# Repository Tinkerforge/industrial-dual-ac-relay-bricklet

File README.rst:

Industrial Dual AC Relay Bricklet
=================================

This repository contains the firmware source code and the hardware design
files. The documentation generator configs can be found at
https://github.com/Tinkerforge/generators

Repository Content
------------------

software/:
 * examples/: Examples for all supported languages
 * build/: Compiled files
 * src/: Source code of firmware
 * Makefile: Makefile to build project

hardware/:
 * Contains KiCad project files and additionally schematics as PDF

datasheets/:
 * Contains datasheets for sensors and complex ICs that are used

Hardware
--------

The hardware is designed with the open source EDA Suite KiCad
(http://www.kicad.org). Before you are able to open the files,
you have to install the Tinkerforge kicad-libraries
(https://github.com/Tinkerforge/kicad-libraries). You can either clone
them directly in hardware/ or clone them in a separate folder and
symlink them into hardware/
(ln -s kicad_path/kicad-libraries project_path/hardware). After that you
can open the .pro file in hardware/ with KiCad and from there view and
modify the schematics and the PCB layout.

Software
--------

If you want to do your own Brick/Bricklet firmware development we highly
recommend that you use our build environment setup script and read the
tutorial (https://www.tinkerforge.com/en/doc/Tutorials/Tutorial_Build_Environment/Tutorial.html).

To compile the C code we recommend you to install the newest GNU Arm Embedded
Toolchain (https://launchpad.net/gcc-arm-embedded/+download).
You also need to install bricklib2 (https://github.com/Tinkerforge/bricklib2).

You can either clone it directly in software/src/ or clone it in a
separate folder and symlink it into software/src/
(ln -s bricklib_path/bricklib2 project_path/software/src/). Finally make sure to
have CMake installed (http://www.cmake.org/cmake/resources/software.html).

After that you can build the firmware by invoking make in software/.
The firmware (.zbin) can then be found in software/build/ and uploaded
with brickv (click button "Flashing" on start screen).

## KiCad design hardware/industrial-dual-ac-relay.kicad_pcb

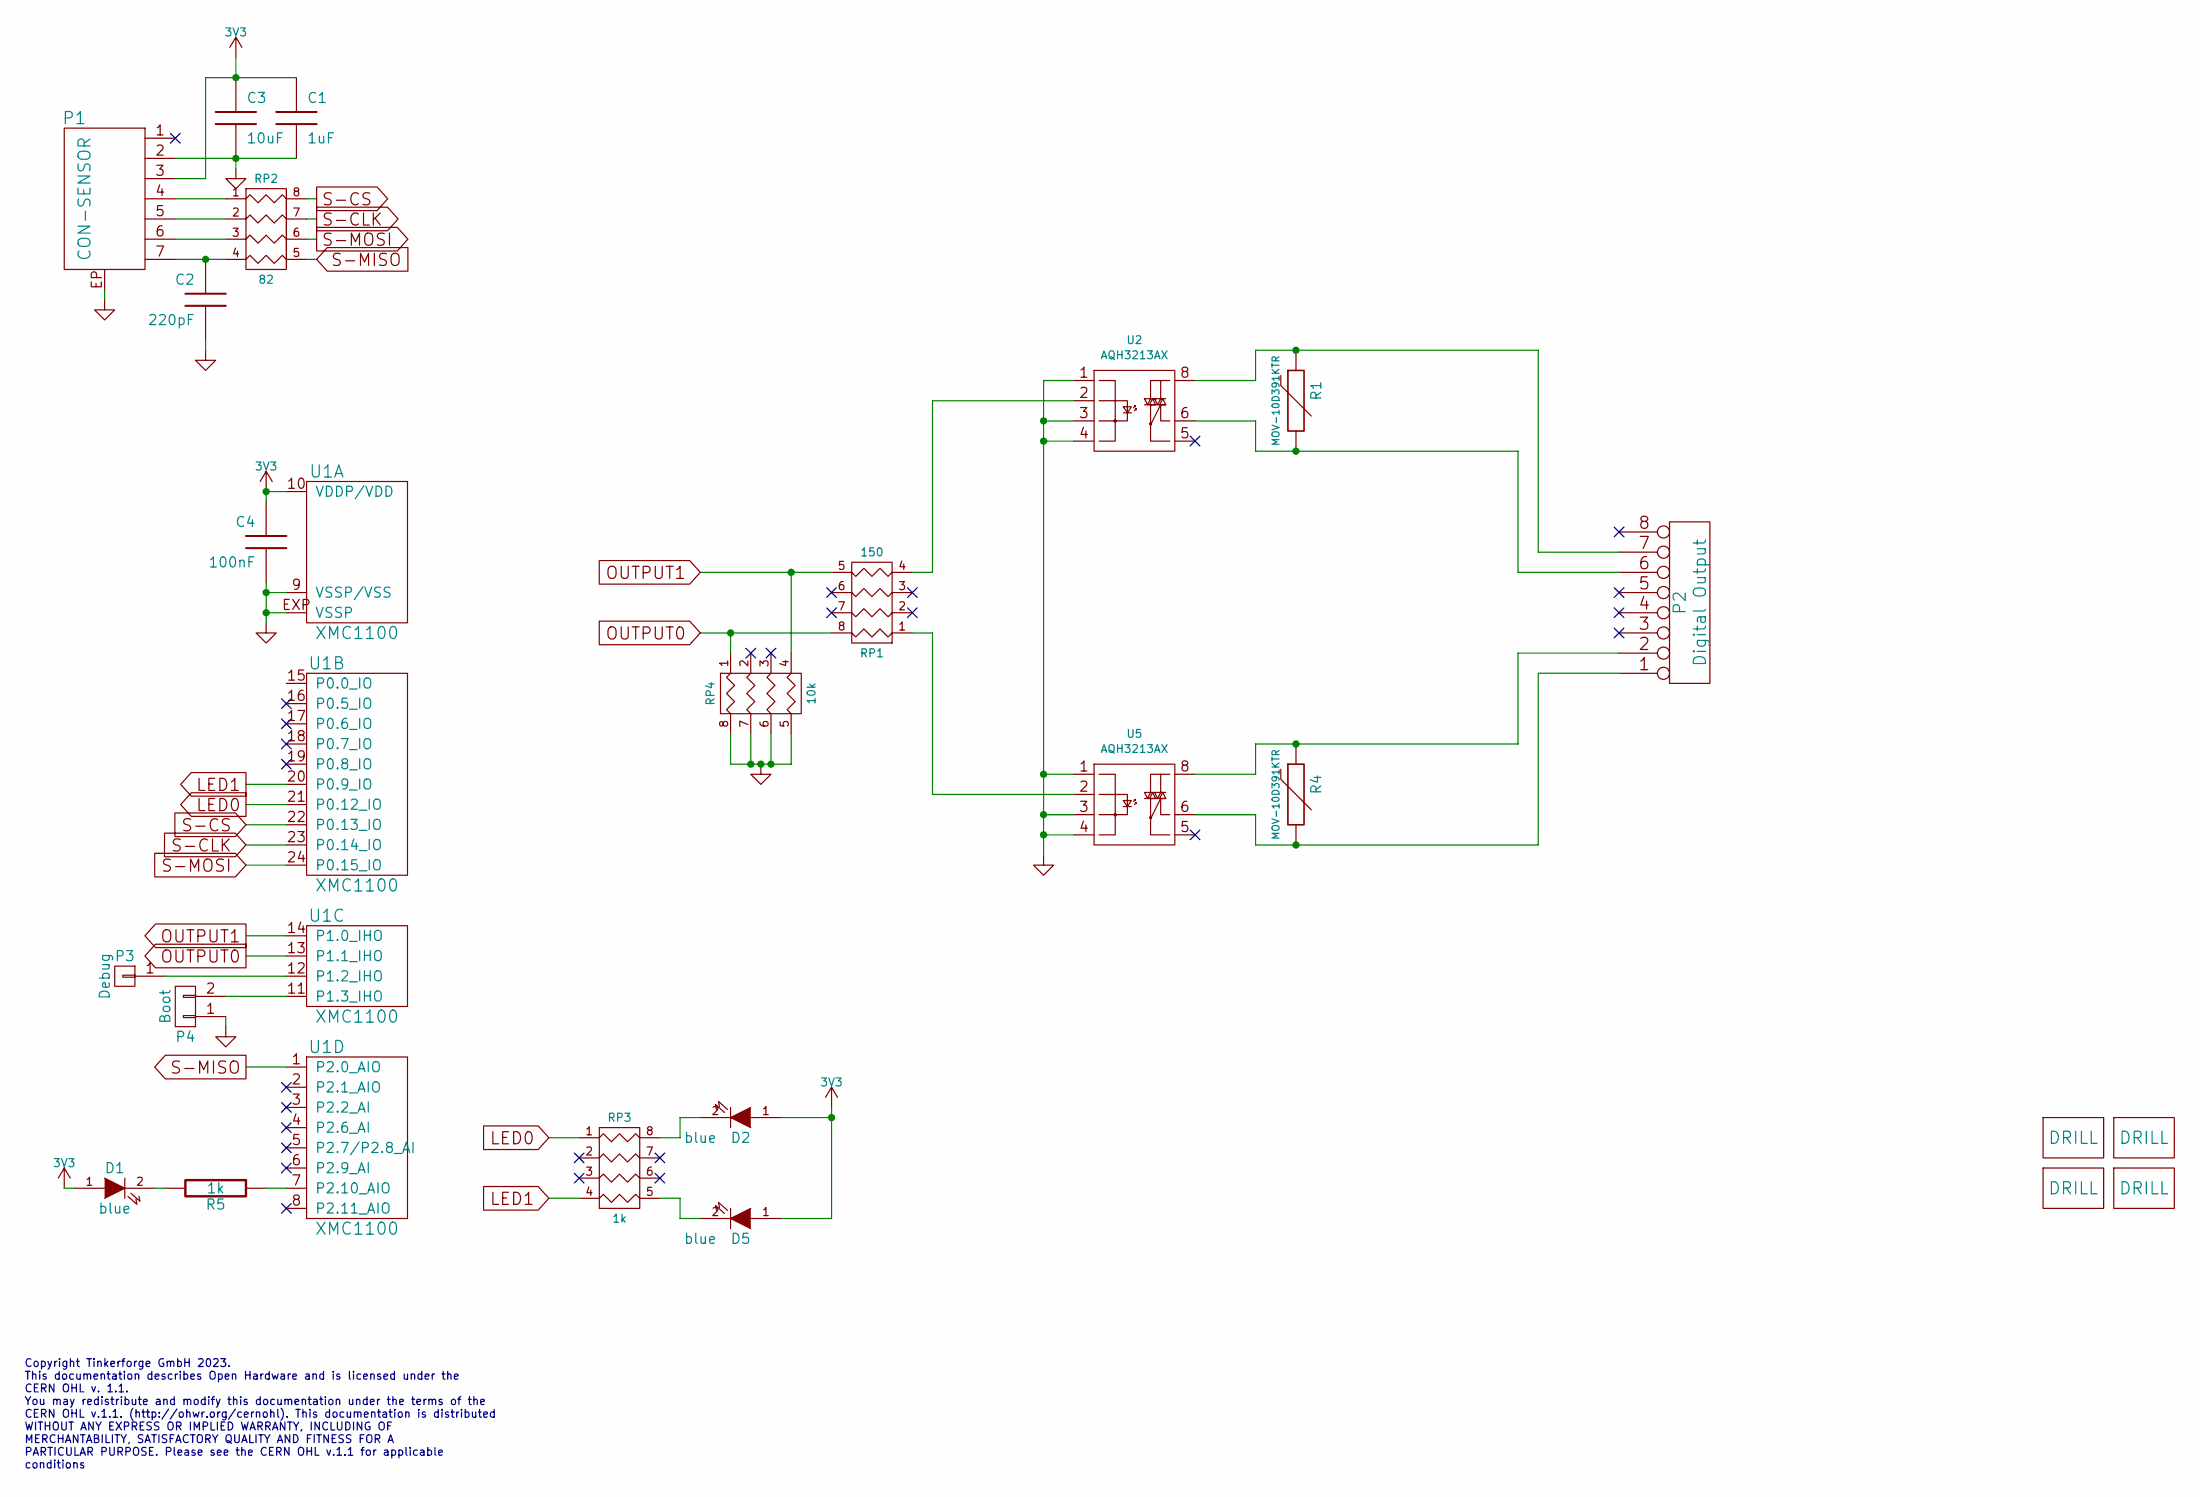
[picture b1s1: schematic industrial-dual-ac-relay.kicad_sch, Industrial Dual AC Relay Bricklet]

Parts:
C1: 1uF; C0603F
C2: 220pF; C0402F
C3: 10uF; C0805
C4: 100nF; C0603F
D1, D2, D5: blue; D0603F
P1: CON-SENSOR; CON-SENSOR2
P2: Digital Output; OQ_8P_230V
P3: Debug; DEBUG_PAD
P4: Boot; SolderJumper
R1, R4: MOV-10D391KTR; VAR_10mm
R5: 1k; R0603F
RP1: 150; 0603X4
RP2: 82; 4X0402
RP3: 1k; 0603X4
RP4: 10k; 0603X4
U1: XMC1100; QFN24-4x4mm-0.5mm
U2, U5: AQH3213AX; AQ-H
U7, U8, U9: DRILL; DRILL_NP
Ue1: DRILL; DRILL_NP

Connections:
3V3: C1.1, C3.1, C4.1, D1.1 (A), D2.1 (A), D5.1 (A), P1.3, U1.10 (VDDP/VDD)
GND: C1.2, C2.2, C3.2, C4.2, P1.2, P1.EP, P4.1, RP4.5 (R4), RP4.6 (R3), RP4.7 (R2), RP4.8 (R1), U1.9 (VSSP/VSS), U1.EXP (VSSP), U2.1, U2.3, U2.4, U5.1, U5.3, U5.4
LED0: RP3.1, U1.21 (P0.12_IO)
LED1: RP3.4, U1.20 (P0.9_IO)
unnamed: C2.1, P1.7, RP2.4
unnamed: D1.2 (K), R5.2
unnamed: D2.2 (K), RP3.8 (R1)
unnamed: D5.2 (K), RP3.5 (R4)
unnamed: P1.4, RP2.1
unnamed: P1.5, RP2.2
unnamed: P1.6, RP2.3
unnamed: P2.1, R4.2, U5.6
unnamed: P2.2, R4.1, U5.8
unnamed: P2.6, R1.2, U2.6
unnamed: P2.7, R1.1, U2.8
unnamed: P3.1, U1.12 (P1.2_IHO)
unnamed: P4.2, U1.11 (P1.3_IHO)
unnamed: R5.1, U1.7 (P2.10_AIO)
unnamed: RP1.1, U5.2
unnamed: RP1.4, U2.2
OUTPUT0: RP1.8 (R1), RP4.1, U1.13 (P1.1_IHO)
OUTPUT1: RP1.5 (R4), RP4.4, U1.14 (P1.0_IHO)
S-CLK: RP2.7 (R2), U1.23 (P0.14_IO)
S-CS: RP2.8 (R1), U1.22 (P0.13_IO)
S-MISO: RP2.5 (R4), U1.1 (P2.0_AIO)
S-MOSI: RP2.6 (R3), U1.24 (P0.15_IO)

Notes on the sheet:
Copyright Tinkerforge GmbH 2023. This documentation describes Open Hardware and is licensed under the CERN OHL v. 1.1. You may redistribute and modify this documentation under the terms of the CERN OHL v.1.1. (http://ohwr.org/cernohl). This documentation is distributed WITHOUT ANY EXPRESS OR IMPLIE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

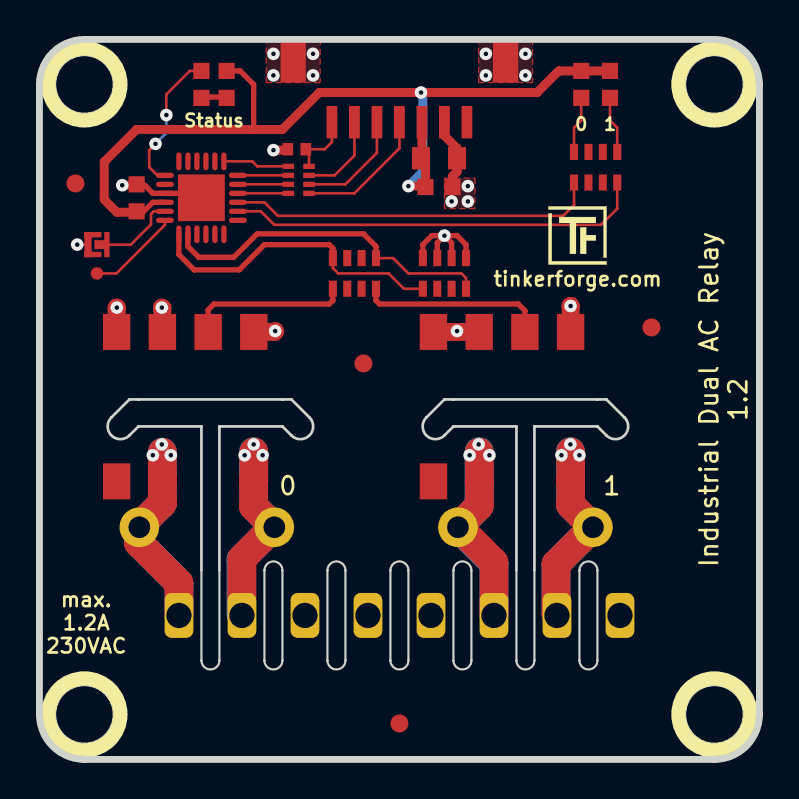
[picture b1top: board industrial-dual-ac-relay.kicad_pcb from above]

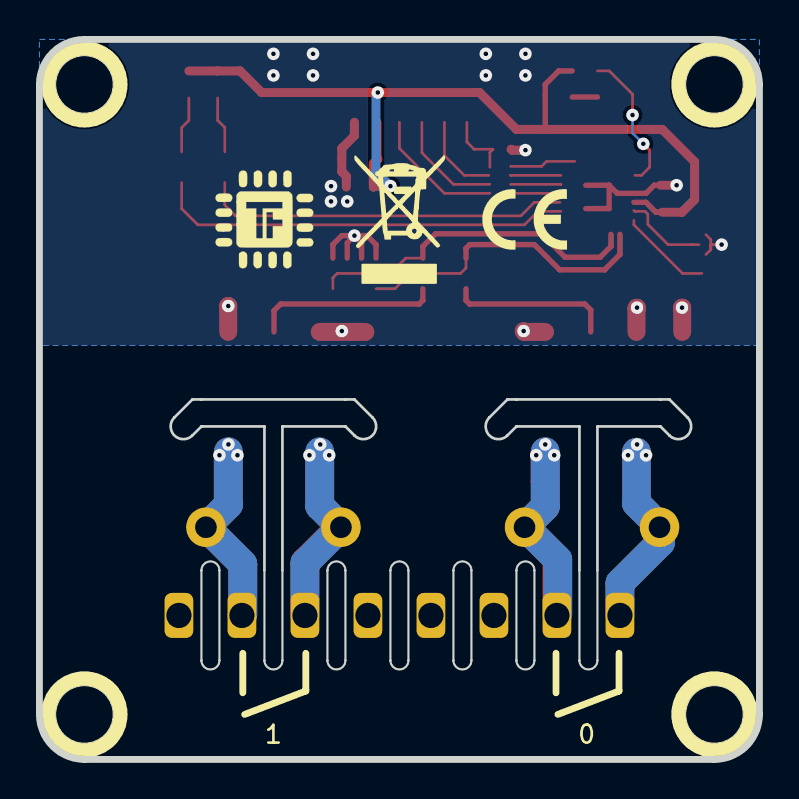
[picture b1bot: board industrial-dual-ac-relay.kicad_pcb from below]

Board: 2 copper layers, 40.0 x 40.0 mm, 31 parts (2 on the bottom side), 26 nets.

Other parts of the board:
Fiducial_Mark: VAL**; Fiducial_Mark
Fiducial_Mark#2, Fiducial_Mark#3, Fiducial_Mark#4: VAL**; Fiducial_Mark
VAL: WEEE_7mm
VAL#2: CE_5mm

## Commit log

2020-08-03 initial push
2020-08-03 added datasheet
2020-08-04 ready for prototype
2020-08-19 Version V1.1 : Changed pins to highoutput, changed resistor order
2020-09-01 Add missing sym-lib-table
2020-09-01 Add Industrial Dual AC Relay Bricklet firmware implementation
2020-09-01 Add support for channel LEDs
2020-09-02 uc: Add example driver note.
2020-09-15 Add examples.
2020-09-17 Fix relay/pin defines
2021-04-28 fix 3d view, add schematic
2021-04-28 add LICENSE
2021-04-28 fix 3d path
2021-04-28 add 3d data
2021-05-03 Add LabVIEW example
2021-05-27 readme: Remove in-development marker
2021-05-27 Update changelog
2021-10-25 Update KiCad link
    https://www.kicad.org/blog/2021/10/Avoid-links-to-former-kicad-domain/
2022-04-19 examples: uc: Rename TF_HalContext to TF_HAL.
2022-04-27 uc: Adapt to bindings changes
2022-07-06 Add license files.
2022-11-15 changed to KiCad 6, changed OQ footprint for more clearence
2022-11-17 extented the clearance slits
2022-11-17 Prototype V1.2
2023-01-23 New standart layout
2023-01-25 Data cleanup
2023-01-30 added fiducials

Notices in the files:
hardware/industrial-dual-ac-relay.kicad_pcb:
Licensed under CERN OHL v.1.1
Copyright (©) 2023, T.Schneidmann
hardware/industrial-dual-ac-relay.kicad_sch:
Copyright (©) 2023, T.Schneidermann
